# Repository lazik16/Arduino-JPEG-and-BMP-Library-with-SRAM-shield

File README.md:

# Arduino-JPEG-and-BMP-Library-with-SRAM-shield

Hello.

About 2 years I worked at the library Shield with support for compression and decompression of raster images (JPEG and BMP). It was a thesis.

I give here a source code and documentation of my work to use and further development.
The thesis is in Czech language codes but the comments are in English.
Also attach files for manufacturing Shield, which has not been verified. I worked on CTE LCD Shield. SRAM has been soldered in place EEPROM. The library is compatible with 8-bit and 32-bit platform with SS pin SRAM modification in the code.

Summary of the thesis:
The diploma thesis is focused on the compression and decompression of the image on the Arduino development platform. The work is divided into four parts. The first part is dedicated to the development platform Arduino. The introduction is a summary of the implementation of the Arduino platform as a tool for compression or decompression of raster image. Furthermore, there is disclosed a development environment and development boards, which were used for this work. The second part discusses the problem of image compression. There are described in detail raster format BMP and JPEG, including operations that take place during compression.

Another chapter deals with the design solution that allows realizing image compression and decompression on this platform. There is described a proposal expansion boards (Shield) containing additional SRAM memory that is compatible with 8 and 32-bit versions of Arduino. Also disclosed is a software solution that takes care of the operation of the Shield and realization of a raster image.

In conclusion, there are tests and experiments that were conducted as to verify the functionality and performance of the solution.

The aim of this work was to create a comprehensive solution for compression and decompression of raster image on the Arduino development platform. It supports BMP file format and basic sequential JPEG compression with color depth of 24 bits.
The entire hardware and software solutions have been tested at 8-bit and 32-bit version of the development platform Arduino.
From tests and experiments suggest that compression and decompression of raster image platform Arduino is realizable. Platform performance (especially 8-bit) is very low, therefore, time-consuming compression or decompression of the image is very high. The big problem is the lack of units working with a decimal point, causing a rapid rise time in the implementation of discrete cosine transform.

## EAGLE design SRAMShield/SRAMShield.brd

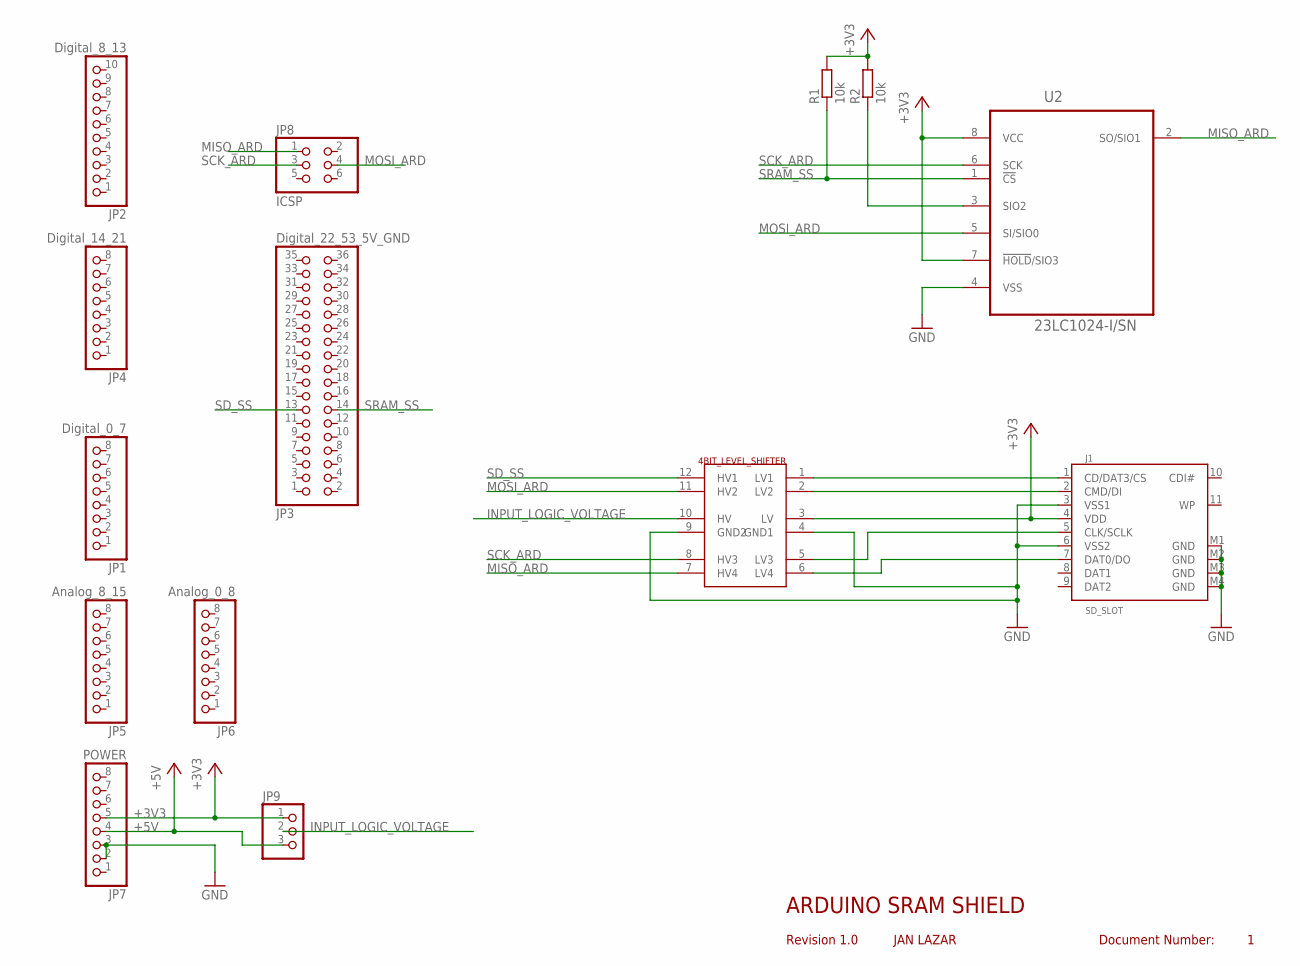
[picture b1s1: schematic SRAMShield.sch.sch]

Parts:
4BIT_LEVEL_SHIFTER: 4BIT_LEVEL_SHIFTER; THT12
J1: SD_SLOT; SDCMF-10915W010
JP1: Digital_0_7; 1X08
JP2: Digital_8_13; 1X10
JP3: Digital_22_53_5V_GND; 2X18
JP4: Digital_14_21; 1X08
JP5: Analog_8_15; 1X08
JP6: Analog_0_8; 1X08
JP7: POWER; 1X08
JP8: ICSP; 2X03
JP9: PINHD-1X3; 1X03
R1, R2: 10k; 0204/7
U2: 23LC1024-I/SN; SOIC127P600X175-8N

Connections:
+3V3: 4BIT_LEVEL_SHIFTER.3 (LV), J1.4 (VDD), JP7.5, JP9.1, R1.2, R2.2, U2.7 (!HOLD!/SIO3), U2.8 (VCC)
+5V: JP7.4, JP9.3
GND: 4BIT_LEVEL_SHIFTER.4 (GND1), 4BIT_LEVEL_SHIFTER.9 (GND2), J1.3 (VSS1), J1.6 (VSS2), J1.M1 (GND), J1.M2 (GND), J1.M3 (GND), J1.M4 (GND), JP7.2, JP7.3, U2.4 (VSS)
INPUT_LOGIC_VOLTAGE: 4BIT_LEVEL_SHIFTER.10 (HV), JP9.2
MISO_ARD: 4BIT_LEVEL_SHIFTER.7 (HV4), JP8.1, U2.2 (SO/SIO1)
MOSI_ARD: 4BIT_LEVEL_SHIFTER.11 (HV2), JP8.4, U2.5 (SI/SIO0)
unnamed: 4BIT_LEVEL_SHIFTER.1 (LV1), J1.1 (CD/DAT3/CS)
unnamed: 4BIT_LEVEL_SHIFTER.2 (LV2), J1.2 (CMD/DI)
unnamed: 4BIT_LEVEL_SHIFTER.5 (LV3), J1.5 (CLK/SCLK)
unnamed: 4BIT_LEVEL_SHIFTER.6 (LV4), J1.7 (DAT0/DO)
unnamed: R2.1, U2.3 (SIO2)
SCK_ARD: 4BIT_LEVEL_SHIFTER.8 (HV3), JP8.3, U2.6 (SCK)
SD_SS: 4BIT_LEVEL_SHIFTER.12 (HV1), JP3.13
SRAM_SS: JP3.14, R1.1, U2.1 (!CS)

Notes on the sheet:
ARDUINO SRAM SHIELD
Revision 1.0
JAN LAZAR
Document Number:

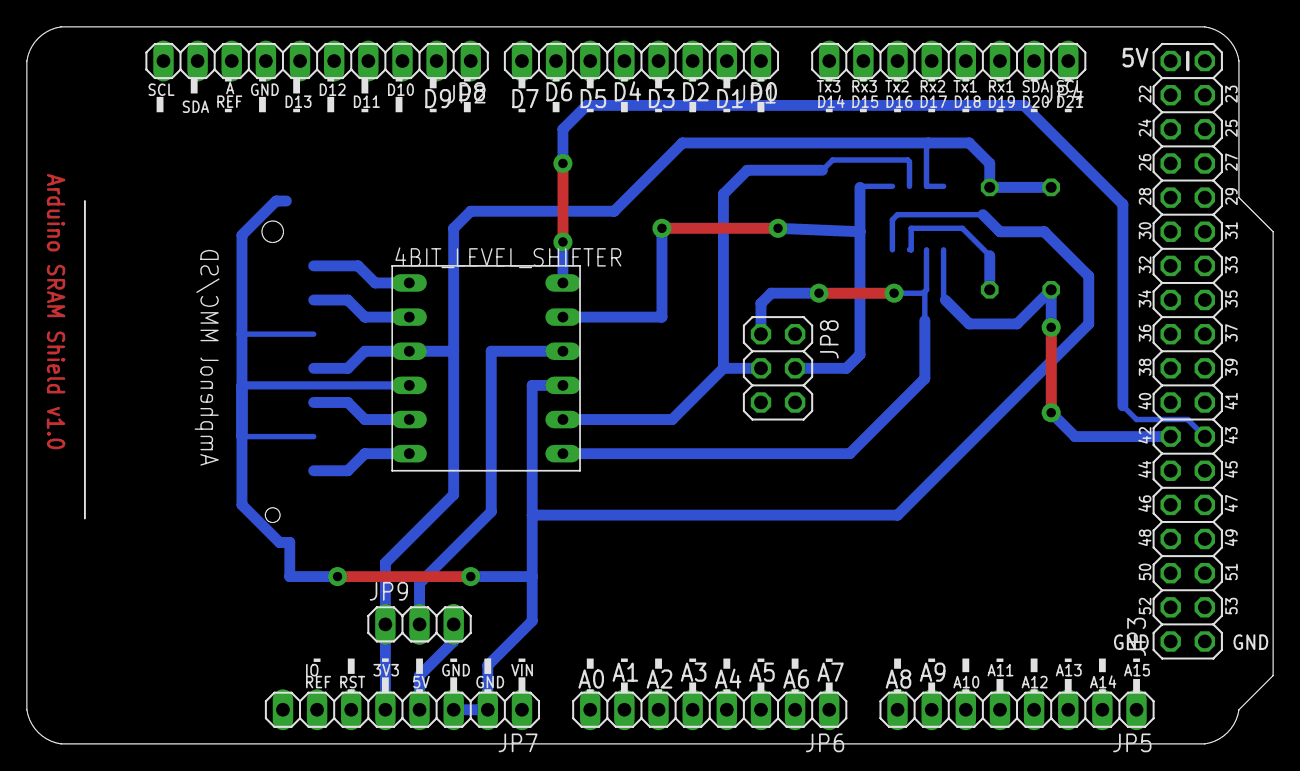
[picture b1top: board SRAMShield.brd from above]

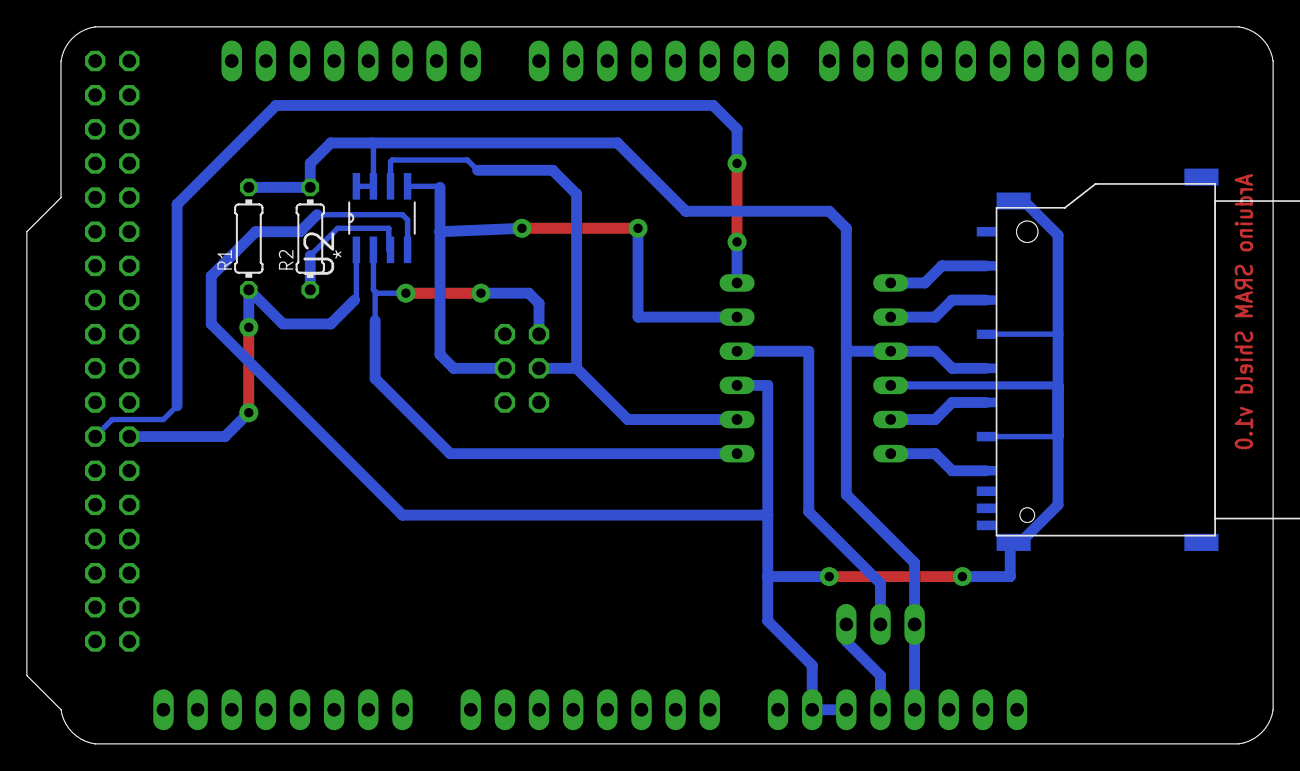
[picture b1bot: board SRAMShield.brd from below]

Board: 2 copper layers, 92.6 x 53.2 mm, 14 parts (4 on the bottom side), 14 nets.

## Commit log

2016-04-19 :octocat: Added .gitattributes & .gitignore files
2016-04-20 Add final document ...
